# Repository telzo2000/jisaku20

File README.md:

# jisaku20

jisaku20 is a 4x5 macro pad keyboard.
<br>
jisaku20は４×５のマクロパッドキーボードです。
<br><br>
By connecting jisaku20 and jisaku20_right with a TRRS cable, it becomes a 40-key split keyboard.Call it jisaku20x2.
<br>
jisaku20とjisaku20_rightをTRRSケーブルで繋ぐことにより、40キーの分割キーボードになります。それをjisaku20x2と呼びます。

<br>
<br>

## firmware

https://github.com/telzo2000/jisaku20/tree/main/firmware

## Case(acrylic plate)

https://github.com/telzo2000/jisaku20/tree/main/case_design

## Parts list

### jisaku20

| No. | Patrs | Quantity | remarks | Suppliers | Cost |
|--|--|--|--|--|--|
|番号|名前|数|備考|調達先|参考価格（送料込）|<br>
|1|PCB|1|20key ortho Layout|[elecrow](https://www.elecrow.com)<br>[JLCPCB](https://jlcpcb.com)<br>[ALLPCB](https://www.allpcb.com)|５枚で10〜20ドル|<br>
|2|Switch Plate|1||[elecrow](https://www.elecrow.com)|５枚で20〜30ドル|<br>
|3|Cover Plate|1|↑|↑|↑|<br>
|4|Bottom Plate|1|↑|↑|↑|<br>
|5|pro micro|1||[Talp Keyboard](https://talpkeyboard.net)|800円|
|6|Swith socket<br>スイッチソケット|20|cherry MX互換|[遊舎工房](https://yushakobo.jp)<br>[Talp Keyboard](https://talpkeyboard.net)<br>[Daily Craft Keyboard](https://shop.dailycraft.jp)等|10個で165円程度|
|7|Diode<br>ダイオード|20|リードタイプでもSMDでも可|[遊舎工房](https://yushakobo.jp)<br>[Talp Keyboard](https://talpkeyboard.net)<br>[Daily Craft Keyboard](https://shop.dailycraft.jp)等|100個で220円程度から|
|7|TRRS jack|1||[遊舎工房](https://yushakobo.jp)<br>[Talp Keyboard](https://talpkeyboard.net)<br>|１個55円|<br>
|8|リセット用タクトスイッチ|1||[遊舎工房](https://yushakobo.jp)<br>[Talp Keyboard](https://talpkeyboard.net)<br>|１個11円|<br>

※When using as jisaku20x2, the total number is doubled and a TRRS cable is required.
<br>
※jisaku20x2として使用する場合、すべての個数が２倍となり、さらに、TRRSケーブルが必要となります。
<br><br>
In addition, you will need a USB cable, keycaps, etc.
<br>
この他に、USBケーブル、キーキャップ等が必要です。
<br>

<br>

## Build guide

https://github.com/telzo2000/jisaku20/blob/main/buildguide_for_jisaku20.md

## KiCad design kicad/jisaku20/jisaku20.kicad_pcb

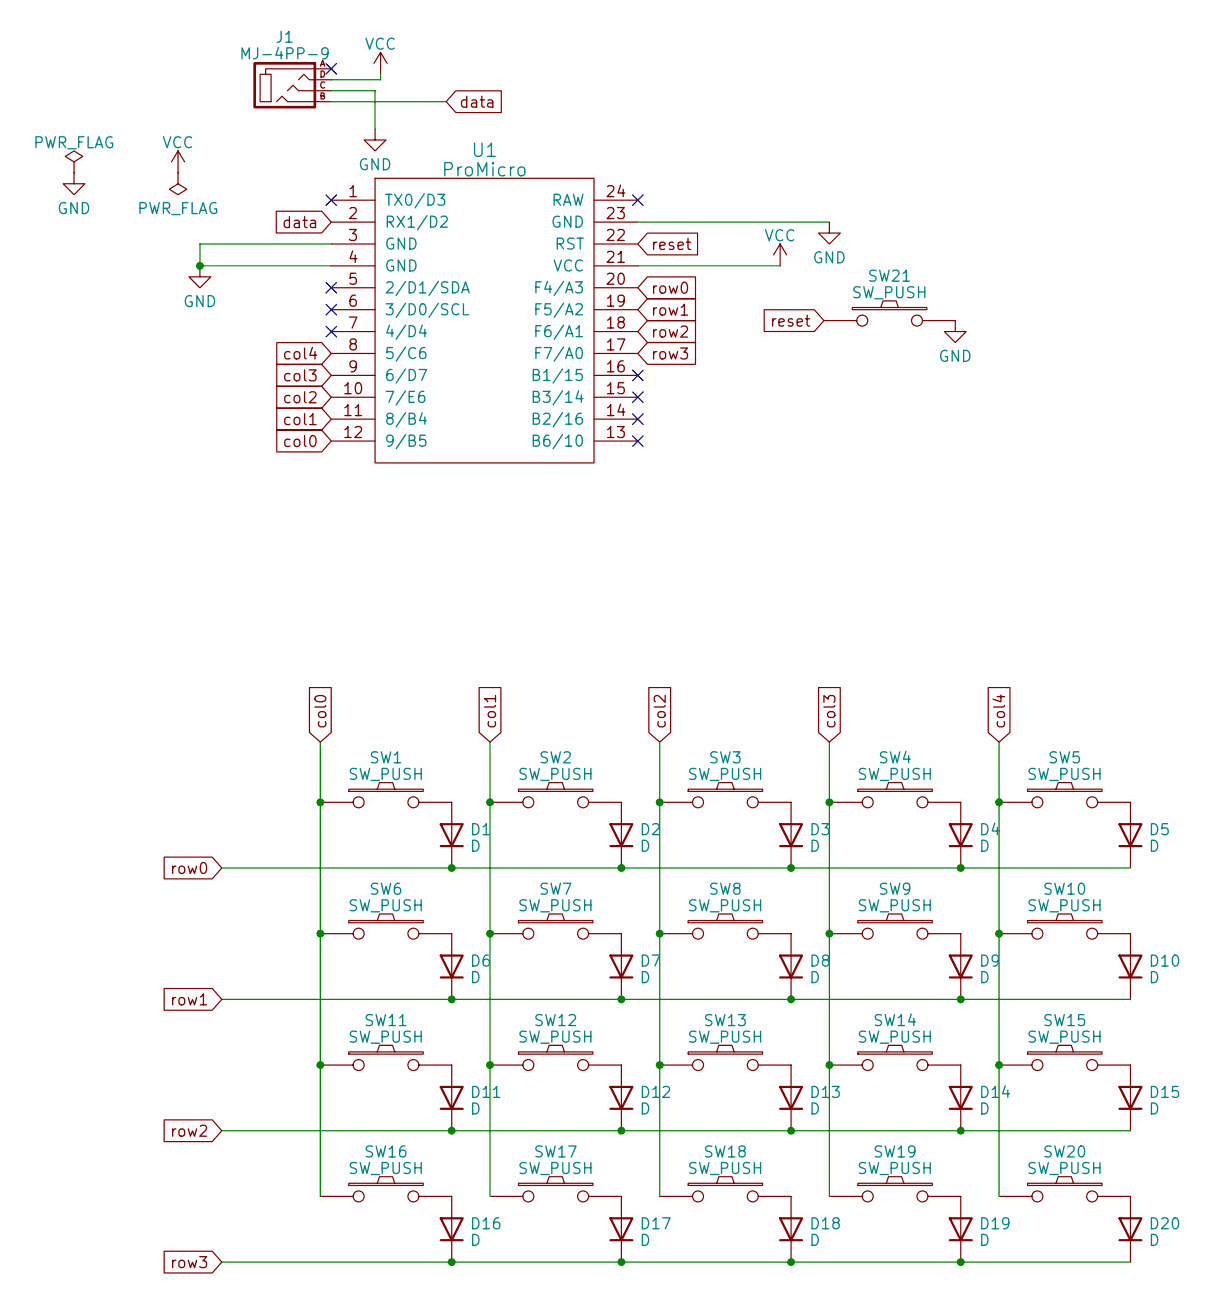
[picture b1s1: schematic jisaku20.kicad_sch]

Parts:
D1, D2, D3, D4, D5, D6, D7, D8, D9, D10, D11, D12, D13, D14, D15, D16, D17, D18, D19, D20: D; D3_TH_SMD_v2
J1: MJ-4PP-9
SW1, SW2, SW3, SW4, SW5, SW6, SW7, SW8, SW9, SW10, SW11, SW12, SW13, SW14, SW15, SW16, SW17, SW18, SW19, SW20: SW_PUSH; CherryMX_Hotswap
SW21: SW_PUSH; ResetSW
U1: ProMicro; ProMicro_v3

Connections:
GND: J1.C, SW21.2, U1.3 (GND), U1.4 (GND), U1.23 (GND)
unnamed: D1.2 (A), SW1.2
unnamed: D2.2 (A), SW2.2
unnamed: D3.2 (A), SW3.2
unnamed: D4.2 (A), SW4.2
unnamed: D5.2 (A), SW5.2
unnamed: D6.2 (A), SW6.2
unnamed: D7.2 (A), SW7.2
unnamed: D8.2 (A), SW8.2
unnamed: D9.2 (A), SW9.2
unnamed: D10.2 (A), SW10.2
unnamed: D11.2 (A), SW11.2
unnamed: D12.2 (A), SW12.2
unnamed: D13.2 (A), SW13.2
unnamed: D14.2 (A), SW14.2
unnamed: D15.2 (A), SW15.2
unnamed: D16.2 (A), SW16.2
unnamed: D17.2 (A), SW17.2
unnamed: D18.2 (A), SW18.2
unnamed: D19.2 (A), SW19.2
unnamed: D20.2 (A), SW20.2
VCC: J1.D, U1.21 (VCC)
col0: SW1.1, SW6.1, SW11.1, SW16.1, U1.12 (9/B5)
col1: SW2.1, SW7.1, SW12.1, SW17.1, U1.11 (8/B4)
col2: SW3.1, SW8.1, SW13.1, SW18.1, U1.10 (7/E6)
col3: SW4.1, SW9.1, SW14.1, SW19.1, U1.9 (6/D7)
col4: SW5.1, SW10.1, SW15.1, SW20.1, U1.8 (5/C6)
data: J1.B, U1.2 (RX1/D2)
reset: SW21.1, U1.22 (RST)
row0: D1.1 (K), D2.1 (K), D3.1 (K), D4.1 (K), D5.1 (K), U1.20 (F4/A3)
row1: D6.1 (K), D7.1 (K), D8.1 (K), D9.1 (K), D10.1 (K), U1.19 (F5/A2)
row2: D11.1 (K), D12.1 (K), D13.1 (K), D14.1 (K), D15.1 (K), U1.18 (F6/A1)
row3: D16.1 (K), D17.1 (K), D18.1 (K), D19.1 (K), D20.1 (K), U1.17 (F7/A0)

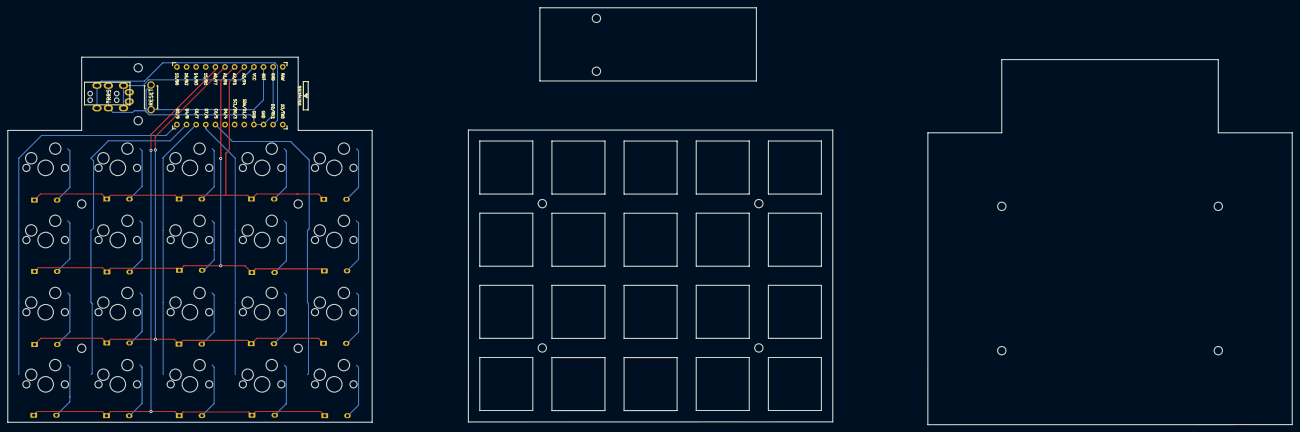
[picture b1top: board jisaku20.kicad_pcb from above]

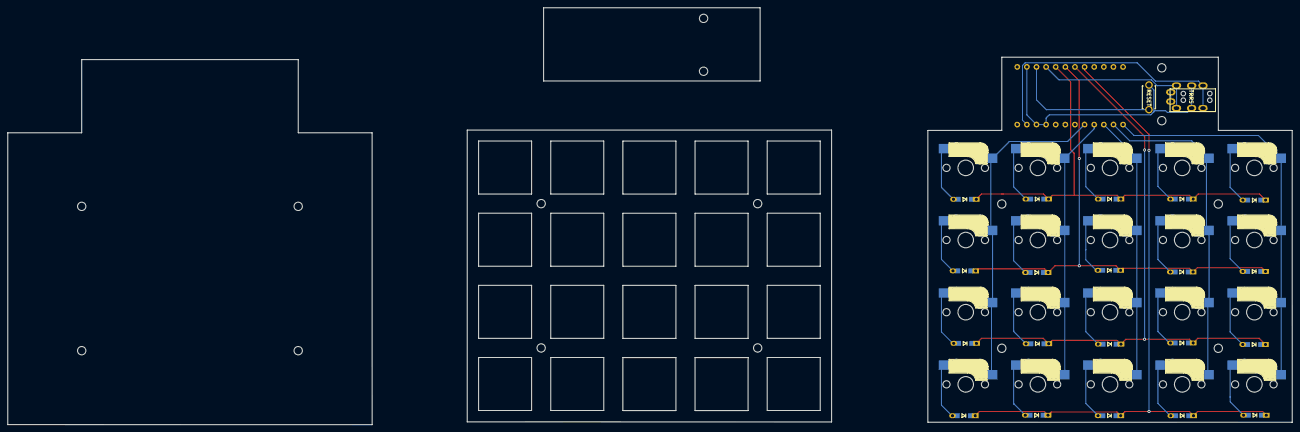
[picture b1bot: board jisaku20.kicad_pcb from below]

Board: 2 copper layers, 96.2 x 96.4 mm, 43 parts (20 on the bottom side), 33 nets.
